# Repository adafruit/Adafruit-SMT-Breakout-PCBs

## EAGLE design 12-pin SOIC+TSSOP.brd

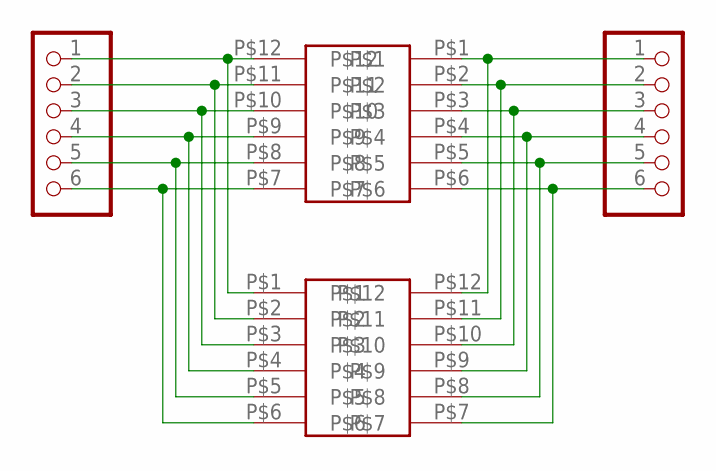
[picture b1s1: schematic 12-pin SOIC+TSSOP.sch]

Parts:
JP1, JP2: PADS-6
U$1: 12-PINTSSOP-NW; TSSOP12-NW
U$2: 12-PINSOIC-NW; SO12-NW

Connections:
unnamed: JP2.2, U$1.P$11, U$2.P$2
unnamed: JP2.3, U$1.P$10, U$2.P$3
unnamed: JP2.4, U$1.P$9, U$2.P$4
unnamed: JP2.5, U$1.P$8, U$2.P$5
unnamed: JP2.6, U$1.P$7, U$2.P$6
unnamed: JP1.1, U$1.P$1, U$2.P$12
unnamed: JP1.2, U$1.P$2, U$2.P$11
unnamed: JP1.3, U$1.P$3, U$2.P$10
unnamed: JP1.4, U$1.P$4, U$2.P$9
unnamed: JP1.5, U$1.P$5, U$2.P$8
unnamed: JP1.6, U$1.P$6, U$2.P$7
unnamed: JP2.1, U$1.P$12, U$2.P$1

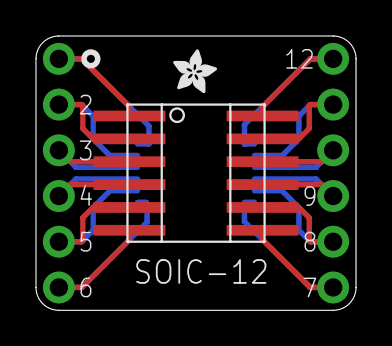
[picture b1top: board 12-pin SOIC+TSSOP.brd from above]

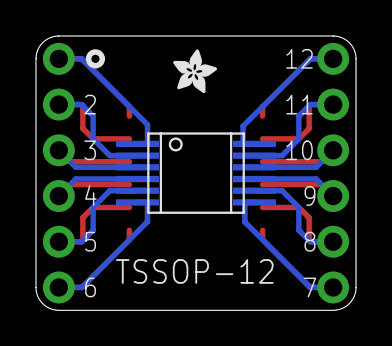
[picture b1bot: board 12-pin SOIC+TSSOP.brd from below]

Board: 2 copper layers, 17.8 x 15.2 mm, 6 parts (2 on the bottom side), 12 nets.

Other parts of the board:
U$3, U$4: ADAFRUIT_2.5MM

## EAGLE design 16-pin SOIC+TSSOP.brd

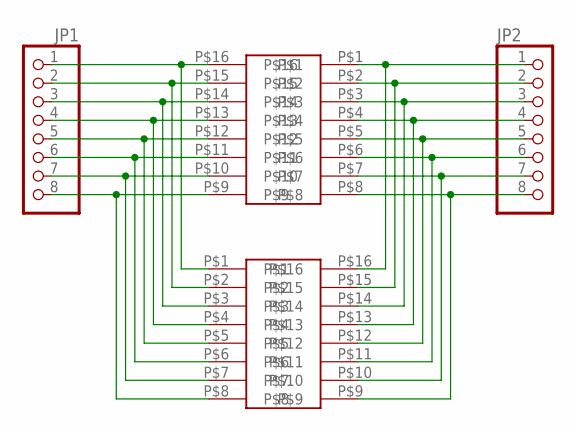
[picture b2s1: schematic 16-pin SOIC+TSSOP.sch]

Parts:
JP1, JP2: PADS-8CLEANBIG; PADS-8
U$1: 16-PINSOIC-NW; SO16-NW
U$2: 16-PINTSSOP-NW; TSSOP16-NW

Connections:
unnamed: JP1.1, U$1.P$1, U$2.P$16
unnamed: JP1.2, U$1.P$2, U$2.P$15
unnamed: JP1.3, U$1.P$3, U$2.P$14
unnamed: JP1.4, U$1.P$4, U$2.P$13
unnamed: JP1.6, U$1.P$6, U$2.P$11
unnamed: JP1.7, U$1.P$7, U$2.P$10
unnamed: JP1.8, U$1.P$8, U$2.P$9
unnamed: JP2.1, U$1.P$16, U$2.P$1
unnamed: JP2.2, U$1.P$15, U$2.P$2
unnamed: JP2.3, U$1.P$14, U$2.P$3
unnamed: JP2.4, U$1.P$13, U$2.P$4
unnamed: JP2.5, U$1.P$12, U$2.P$5
unnamed: JP2.6, U$1.P$11, U$2.P$6
unnamed: JP2.7, U$1.P$10, U$2.P$7
unnamed: JP2.8, U$1.P$9, U$2.P$8
unnamed: JP1.5, U$1.P$5, U$2.P$12

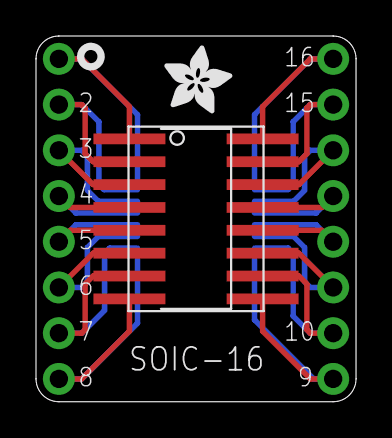
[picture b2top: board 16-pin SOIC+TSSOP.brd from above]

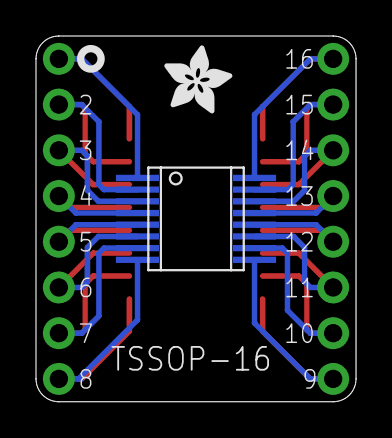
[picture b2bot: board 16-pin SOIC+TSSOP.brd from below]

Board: 2 copper layers, 17.8 x 20.3 mm, 6 parts (2 on the bottom side), 16 nets.

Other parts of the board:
U$3, U$4: ADAFRUIT_3.5MM

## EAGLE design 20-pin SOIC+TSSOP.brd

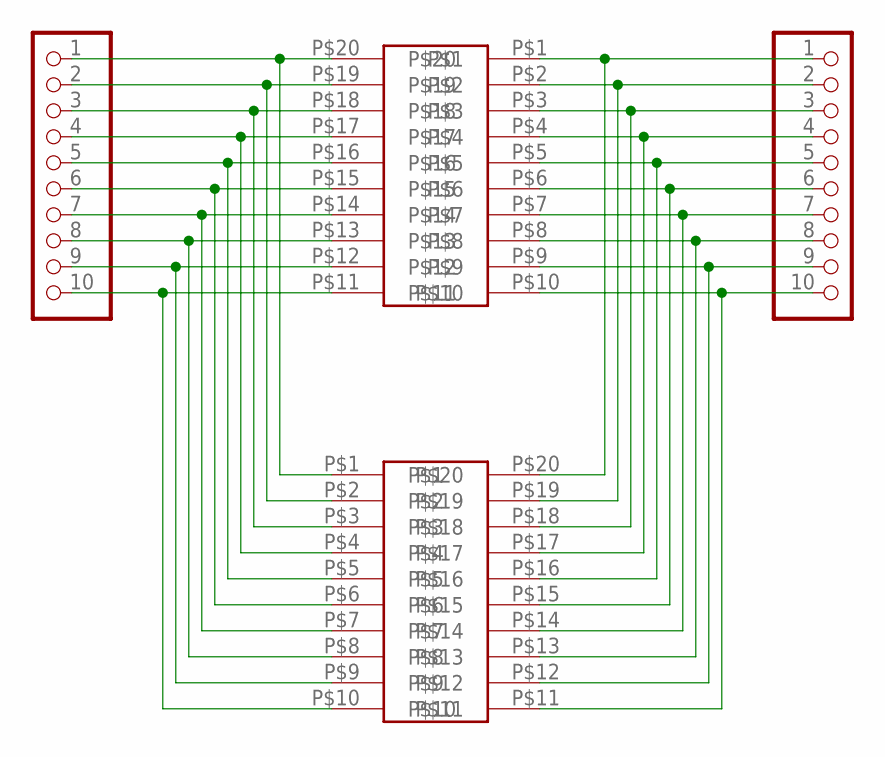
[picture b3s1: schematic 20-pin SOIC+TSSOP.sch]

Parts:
U$1: 20-PINSOIC-NW; SO20-NW
U$2: 20-PINTSSOP-NW; TSSOP20-NW
U$3, U$4: PADS-10

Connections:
unnamed: U$1.P$1, U$2.P$20, U$3.1
unnamed: U$1.P$2, U$2.P$19, U$3.2
unnamed: U$1.P$3, U$2.P$18, U$3.3
unnamed: U$1.P$4, U$2.P$17, U$3.4
unnamed: U$1.P$5, U$2.P$16, U$3.5
unnamed: U$1.P$6, U$2.P$15, U$3.6
unnamed: U$1.P$7, U$2.P$14, U$3.7
unnamed: U$1.P$8, U$2.P$13, U$3.8
unnamed: U$1.P$9, U$2.P$12, U$3.9
unnamed: U$1.P$10, U$2.P$11, U$3.10
unnamed: U$1.P$20, U$2.P$1, U$4.1
unnamed: U$1.P$19, U$2.P$2, U$4.2
unnamed: U$1.P$18, U$2.P$3, U$4.3
unnamed: U$1.P$17, U$2.P$4, U$4.4
unnamed: U$1.P$16, U$2.P$5, U$4.5
unnamed: U$1.P$15, U$2.P$6, U$4.6
unnamed: U$1.P$14, U$2.P$7, U$4.7
unnamed: U$1.P$13, U$2.P$8, U$4.8
unnamed: U$1.P$12, U$2.P$9, U$4.9
unnamed: U$1.P$11, U$2.P$10, U$4.10

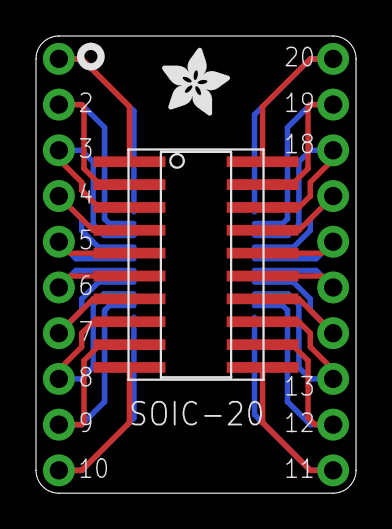
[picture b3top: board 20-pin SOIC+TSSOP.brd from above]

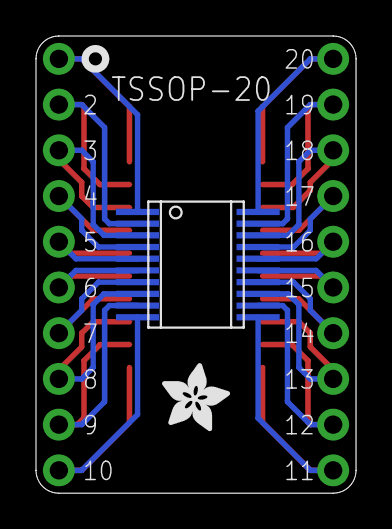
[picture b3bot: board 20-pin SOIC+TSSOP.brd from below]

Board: 2 copper layers, 17.8 x 25.4 mm, 6 parts (2 on the bottom side), 20 nets.

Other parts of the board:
U$5, U$6: ADAFRUIT_3.5MM

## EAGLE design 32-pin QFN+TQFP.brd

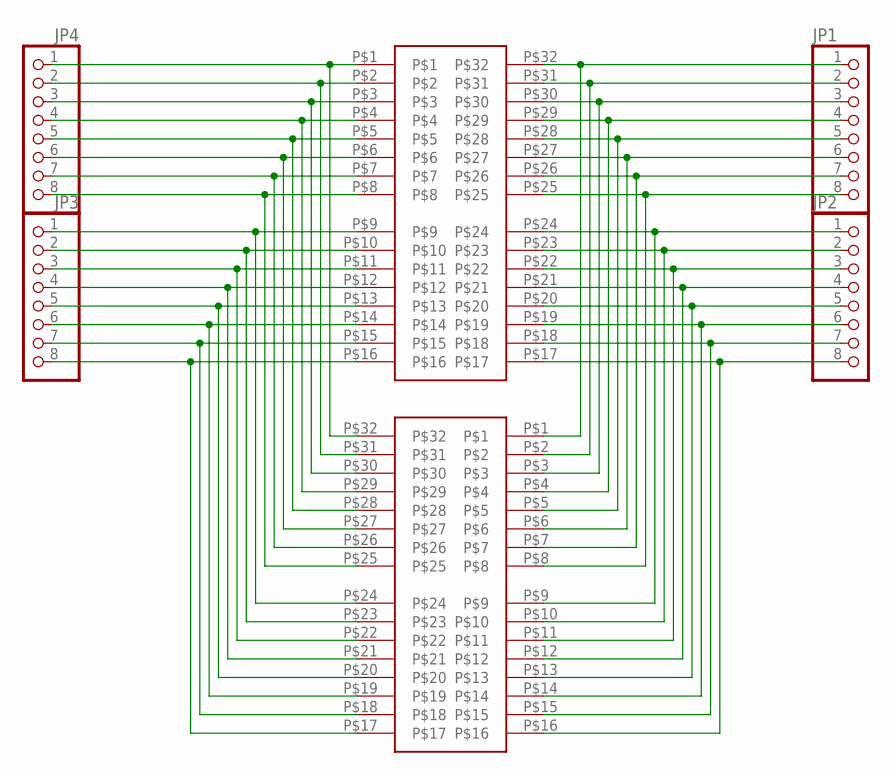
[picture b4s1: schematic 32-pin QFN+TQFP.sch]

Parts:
JP1, JP2, JP3, JP4: PADS-8CLEANBIG; PADS-8
U$1: 32-PINQFN; QFN32
U$2: 32-PINTQFP; TQFP32-08

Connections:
unnamed: JP4.1, U$1.P$1, U$2.P$32
unnamed: JP4.2, U$1.P$2, U$2.P$31
unnamed: JP4.3, U$1.P$3, U$2.P$30
unnamed: JP4.4, U$1.P$4, U$2.P$29
unnamed: JP4.5, U$1.P$5, U$2.P$28
unnamed: JP4.6, U$1.P$6, U$2.P$27
unnamed: JP4.7, U$1.P$7, U$2.P$26
unnamed: JP4.8, U$1.P$8, U$2.P$25
unnamed: JP3.1, U$1.P$9, U$2.P$24
unnamed: JP3.2, U$1.P$10, U$2.P$23
unnamed: JP3.3, U$1.P$11, U$2.P$22
unnamed: JP3.4, U$1.P$12, U$2.P$21
unnamed: JP3.5, U$1.P$13, U$2.P$20
unnamed: JP3.6, U$1.P$14, U$2.P$19
unnamed: JP3.7, U$1.P$15, U$2.P$18
unnamed: JP3.8, U$1.P$16, U$2.P$17
unnamed: JP1.1, U$1.P$32, U$2.P$1
unnamed: JP1.2, U$1.P$31, U$2.P$2
unnamed: JP1.3, U$1.P$30, U$2.P$3
unnamed: JP1.4, U$1.P$29, U$2.P$4
unnamed: JP1.5, U$1.P$28, U$2.P$5
unnamed: JP1.6, U$1.P$27, U$2.P$6
unnamed: JP1.7, U$1.P$26, U$2.P$7
unnamed: JP1.8, U$1.P$25, U$2.P$8
unnamed: JP2.1, U$1.P$24, U$2.P$9
unnamed: JP2.2, U$1.P$23, U$2.P$10
unnamed: JP2.3, U$1.P$22, U$2.P$11
unnamed: JP2.4, U$1.P$21, U$2.P$12
unnamed: JP2.5, U$1.P$20, U$2.P$13
unnamed: JP2.6, U$1.P$19, U$2.P$14
unnamed: JP2.7, U$1.P$18, U$2.P$15
unnamed: JP2.8, U$1.P$17, U$2.P$16

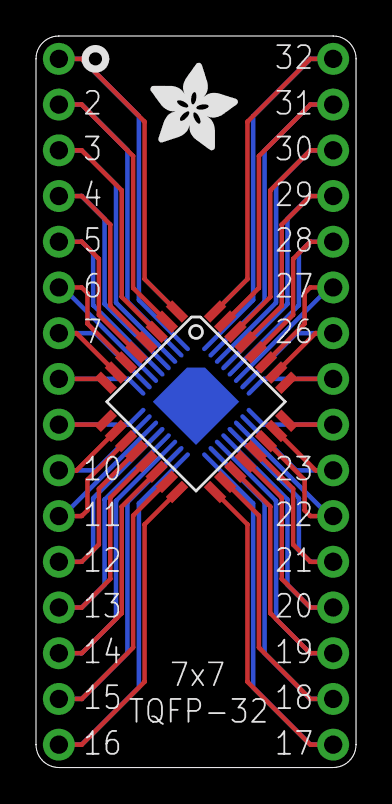
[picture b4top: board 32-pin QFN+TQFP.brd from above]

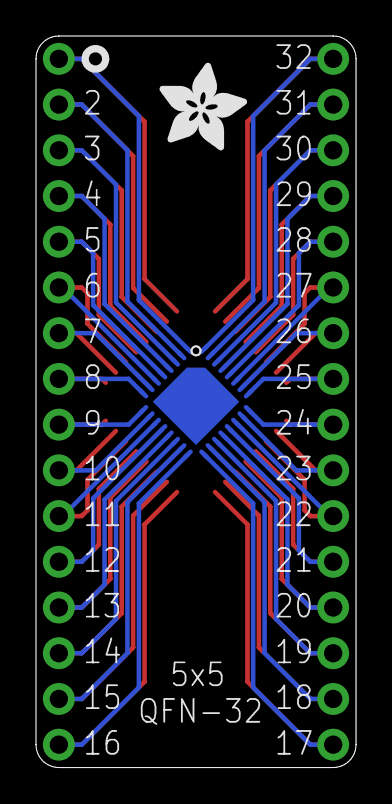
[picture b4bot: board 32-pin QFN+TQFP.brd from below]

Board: 2 copper layers, 17.8 x 40.6 mm, 8 parts (2 on the bottom side), 32 nets.

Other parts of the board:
U$3, U$4: ADAFRUIT_5MM

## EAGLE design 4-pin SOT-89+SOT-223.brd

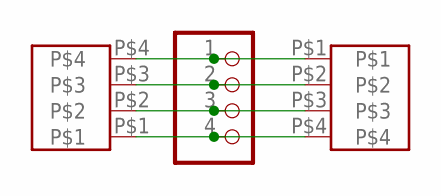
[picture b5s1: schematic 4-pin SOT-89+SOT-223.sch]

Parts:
JP1: PADS-4
U$1: SOT89
U$2: SOT223

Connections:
unnamed: JP1.1, U$1.P$1, U$2.P$4
unnamed: JP1.2, U$1.P$2, U$2.P$3
unnamed: JP1.3, U$1.P$3, U$2.P$2
unnamed: JP1.4, U$1.P$4, U$2.P$1

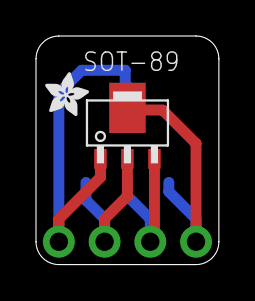
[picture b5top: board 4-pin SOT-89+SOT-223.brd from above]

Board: 2 copper layers, 10.2 x 12.7 mm, 4 parts (1 on the bottom side), 4 nets.

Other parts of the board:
U$3: ADAFRUIT_2.5MM

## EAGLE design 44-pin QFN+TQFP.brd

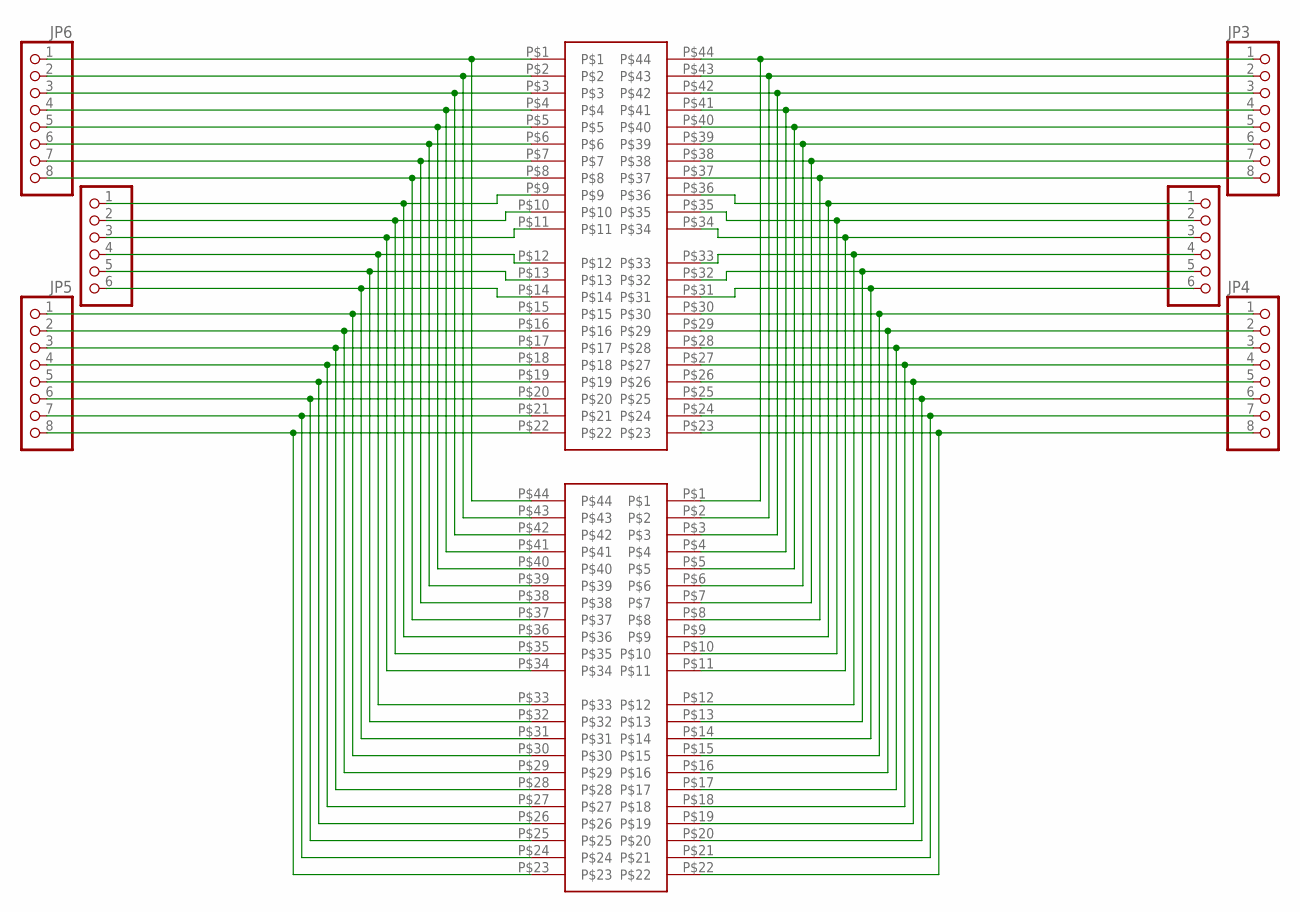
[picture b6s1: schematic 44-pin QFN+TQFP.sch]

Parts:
JP1, JP2: PADS-6
JP3, JP4, JP5, JP6: PADS-8CLEANBIG; PADS-8
U$1: 44-PINQFN; QFN44
U$2: 44-PINTQFP; TQFP44

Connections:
unnamed: JP6.1, U$1.P$1, U$2.P$44
unnamed: JP6.2, U$1.P$2, U$2.P$43
unnamed: JP6.3, U$1.P$3, U$2.P$42
unnamed: JP6.4, U$1.P$4, U$2.P$41
unnamed: JP6.5, U$1.P$5, U$2.P$40
unnamed: JP6.6, U$1.P$6, U$2.P$39
unnamed: JP6.7, U$1.P$7, U$2.P$38
unnamed: JP6.8, U$1.P$8, U$2.P$37
unnamed: JP5.1, U$1.P$15, U$2.P$30
unnamed: JP5.2, U$1.P$16, U$2.P$29
unnamed: JP5.3, U$1.P$17, U$2.P$28
unnamed: JP5.4, U$1.P$18, U$2.P$27
unnamed: JP5.5, U$1.P$19, U$2.P$26
unnamed: JP5.6, U$1.P$20, U$2.P$25
unnamed: JP5.7, U$1.P$21, U$2.P$24
unnamed: JP5.8, U$1.P$22, U$2.P$23
unnamed: JP4.1, U$1.P$30, U$2.P$15
unnamed: JP4.2, U$1.P$29, U$2.P$16
unnamed: JP4.3, U$1.P$28, U$2.P$17
unnamed: JP4.4, U$1.P$27, U$2.P$18
unnamed: JP4.5, U$1.P$26, U$2.P$19
unnamed: JP4.6, U$1.P$25, U$2.P$20
unnamed: JP4.7, U$1.P$24, U$2.P$21
unnamed: JP4.8, U$1.P$23, U$2.P$22
unnamed: JP3.1, U$1.P$44, U$2.P$1
unnamed: JP3.2, U$1.P$43, U$2.P$2
unnamed: JP3.3, U$1.P$42, U$2.P$3
unnamed: JP3.4, U$1.P$41, U$2.P$4
unnamed: JP3.5, U$1.P$40, U$2.P$5
unnamed: JP3.6, U$1.P$39, U$2.P$6
unnamed: JP3.7, U$1.P$38, U$2.P$7
unnamed: JP3.8, U$1.P$37, U$2.P$8
unnamed: JP1.4, U$1.P$33, U$2.P$12
unnamed: JP1.5, U$1.P$32, U$2.P$13
unnamed: JP1.6, U$1.P$31, U$2.P$14
unnamed: JP1.3, U$1.P$34, U$2.P$11
unnamed: JP1.2, U$1.P$35, U$2.P$10
unnamed: JP1.1, U$1.P$36, U$2.P$9
unnamed: JP2.3, U$1.P$11, U$2.P$34
unnamed: JP2.2, U$1.P$10, U$2.P$35
unnamed: JP2.1, U$1.P$9, U$2.P$36
unnamed: JP2.4, U$1.P$12, U$2.P$33
unnamed: JP2.5, U$1.P$13, U$2.P$32
unnamed: JP2.6, U$1.P$14, U$2.P$31

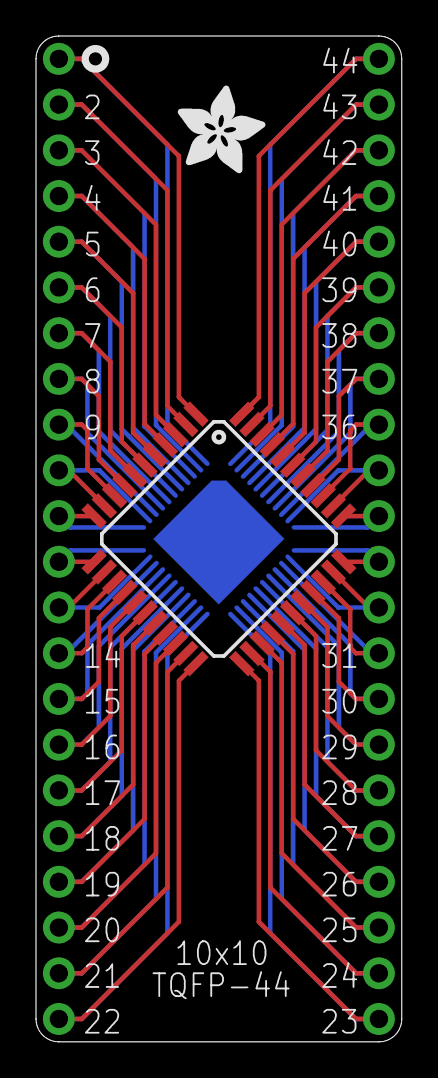
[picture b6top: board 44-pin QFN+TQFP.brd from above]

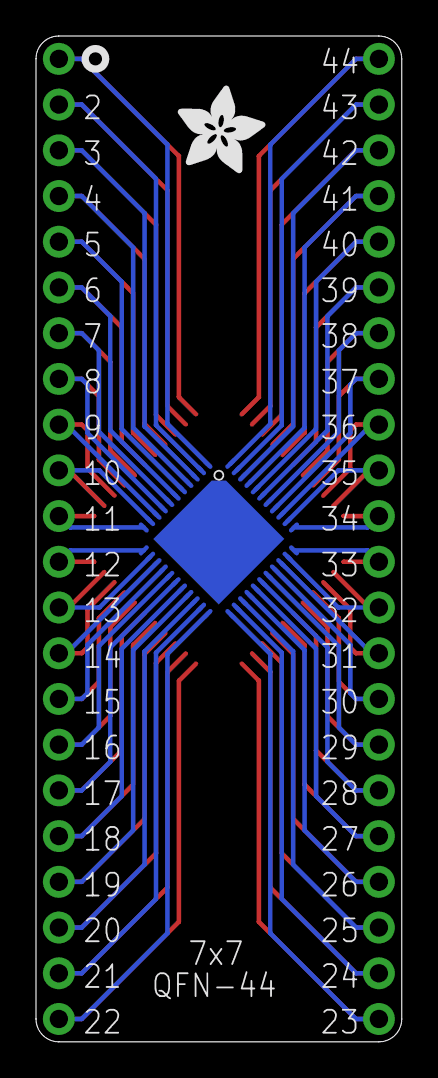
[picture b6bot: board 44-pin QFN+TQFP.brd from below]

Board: 2 copper layers, 20.3 x 55.9 mm, 10 parts (2 on the bottom side), 44 nets.

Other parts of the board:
U$3, U$4: ADAFRUIT_5MM

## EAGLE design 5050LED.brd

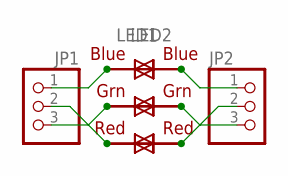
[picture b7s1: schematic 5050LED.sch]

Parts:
JP1, JP2: PINHD-1X3CB; 1X03-CLEANBIG
LED1, LED2: RGBLED5050

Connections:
unnamed: JP1.1, LED1.3 (BLUE_A), LED2.4 (BLUE_C)
unnamed: JP1.2, LED1.2 (RED_A), LED2.5 (RED_C)
unnamed: JP1.3, LED1.1 (GREEN_A), LED2.6 (GREEN_C)
unnamed: JP2.1, LED1.4 (BLUE_C), LED2.3 (BLUE_A)
unnamed: JP2.2, LED1.5 (RED_C), LED2.2 (RED_A)
unnamed: JP2.3, LED1.6 (GREEN_C), LED2.1 (GREEN_A)

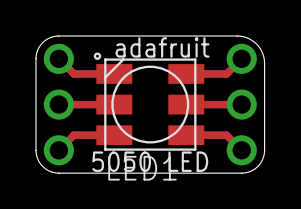
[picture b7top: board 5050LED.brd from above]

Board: 2 copper layers, 12.7 x 7.6 mm, 4 parts (1 on the bottom side), 6 nets.

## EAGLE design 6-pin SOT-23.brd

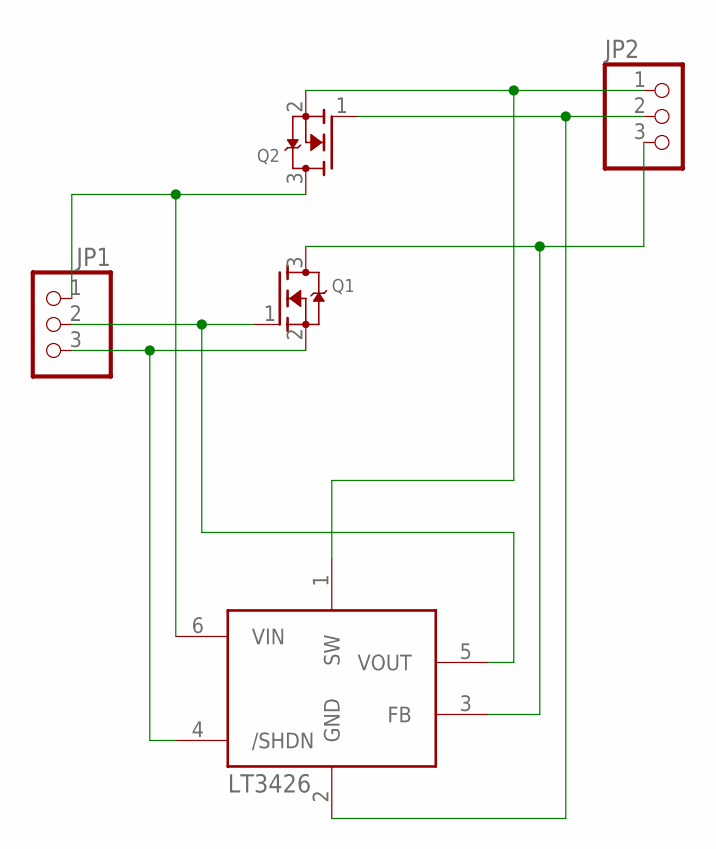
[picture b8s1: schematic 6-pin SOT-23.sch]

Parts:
JP1, JP2: PINHD-1X3CB; 1X03-CLEANBIG
Q1, Q2: MOSFET-NREFLOW; SOT23
U$1: LT3426; SOT23-6

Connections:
GND: JP2.2, Q2.1 (G), U$1.2 (GND)
unnamed: JP2.3, Q1.3 (D), U$1.3 (FB)
unnamed: JP1.2, Q1.1 (G), U$1.5 (VOUT)
unnamed: JP1.3, Q1.2 (S), U$1.4 (/SHDN)
unnamed: JP2.1, Q2.2 (S), U$1.1 (SW)
unnamed: JP1.1, Q2.3 (D), U$1.6 (VIN)

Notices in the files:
parts and their libraries:
microbuilder: This work is placed in the public domain, and may be freely used for commercial and non-commercial work with the following conditions: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
